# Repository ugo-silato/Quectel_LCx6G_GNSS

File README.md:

# Quectel_LCx6G_GNSS

Arduino library for the **Quectel LC26G, LC26G-T, LC76G and LC86G**
multi-constellation GNSS modules (GPS, GLONASS, Galileo, BeiDou, QZSS),
which share the same Quectel protocol (PAIR / PQTM commands).

Developed and tested on the **LC76G (PA)**: that is why the classes and
the main header are called `LC76G` and `Quectel_LC76G.h`. The other
modules of the family are compatible but not tested, see
[Compatible modules and limitations](#compatible-modules-and-limitations).

> **About the hardware.** The shield in the pictures is the **revision 1
> test prototype** used to develop and test this library: it is **not the
> final design**. An improved revision 2 will follow, fixing the issues
> listed in [Reference shield, revision 1 – known issues](#reference-shield-revision-1--known-issues).
> The library itself does not depend on this board: any LC76G wiring works.
> The KiCad 10 files of the shield (schematic, PCB, BOM) are in
> [hardware](hardware/README.md).

> **Status: 1.0.0.** Every function was tested on the bench with real
> hardware (LC76G (PA) on Arduino Uno R3 and Uno R4 Minima), except the
> few listed under [Test status](#test-status), which need outdoor or
> laboratory tests.

## Features

- UART link through any Arduino `Stream` (`HardwareSerial` or `SoftwareSerial`)
- **I2C link** as an alternative to the UART (`LC76G_I2C`, header-only, used
  like a serial port: every function of the library works the same way)
- Automatic UART baud rate configuration: a brand-new module (115200 baud) is
  switched to the speed you choose, e.g. 38400 for `SoftwareSerial`
- NMEA decoder for **RMC**, **GGA** and **GSV**, integer-only
  (latitude/longitude in degrees × 10⁷, no float precision loss on AVR)
- Satellites in view per constellation and strongest signal (SNR)
- End-of-epoch callback, called once per second
- **PAIR** commands with automatic checksum, acknowledgement (`$PAIR001`)
  handling and query results
- Hot / warm / cold start, baud rate query and change
- NMEA output configuration: choose which sentences are sent and how often,
  or keep only the ones the decoder needs (about 30% less UART traffic with a fix)
- Save the configuration to the module flash
- Constellation selection (GPS, GLONASS, Galileo, BDS, QZSS), limited to
  the combinations supported by the LC76G
- Jamming detection: status messages decoded automatically, optional
  reading of the JAM_IND pin
- PQTM proprietary commands with OK/ERROR handling, PQTM message rates
  (set and read back)
- Output settings: minimum satellite SNR, NMEA decimal places and Talker
  ID, RTCM 3 output configuration (the binary RTCM data itself is not
  decoded), Galileo Return Link Message output, 1PPS / NMEA synchronisation
- PQTM output messages decoded through callbacks, integer-only:
  **PQTMPVT** (position, velocity and time), **PQTMVEL** (velocity with
  accuracy estimates), **PQTMDOP** (all dilution of precision values),
  **PQTMODO** (odometer, with configuration and reset), **PQTMTIMEGPS**
  (GPS week and time of week with accuracy), **PQTMPL** (protection
  levels), **PQTMPOSECEF / PQTMVELECEF / PQTMPVTECEF** (ECEF coordinates).
  A message that is not used costs no RAM and no flash
- Geofence: up to 4 circles or polygons, status messages decoded
  automatically, optional reading of the GEOFENCE pin
- 1PPS (One Pulse Per Second) configuration, and optional pulse measurement
  (count, period, width) on an Arduino interrupt pin
- Low power: navigation mode, ALP (Adaptive Low Power), GLP (GPS Low
  Power), FLP (Fitness Low Power), periodic run/sleep, Backup mode with
  automatic VCC cut and wake-up through the power and reset pins
- AGNSS (Assisted GNSS) without internet: EASY and EPOC orbit prediction,
  navigation data save/clear, reference time and position injection,
  firmware version query
- LOCUS built-in logger (128 KB): modes, thresholds, record count, read-back,
  automatic protection of the recorded data on reboot / power-off
- Reception settings: elevation mask, AIC (Active Interference
  Cancellation), SBAS / DGPS corrections, 2D fix, real-time speed response,
  BDS B1C band, static navigation threshold
- Estimated positioning error (PQTMEPE) in metres, factory reset and
  parameter save (PQTMRESTOREPAR / PQTMSAVEPAR)
- Readable full names for results, NMEA sentences and constellations
- Safe control of the module power and reset pins, with three drive modes
  for different hardware designs
- No dynamic memory, no `String` objects

## Supported boards

| Board | Status |
|---|---|
| Arduino Uno R3 (ATmega328P) | Tested (UART through SoftwareSerial, I2C) |
| Arduino Uno R4 Minima | Tested (UART through Serial1 on D0/D1, I2C); all examples select Serial1 automatically, see "Serial port on the Uno R4" |
| Arduino Uno R4 WiFi | Same core as the Minima, not tested |

On the Uno R3 the `BasicMonitor` example uses about 16.5 KB of flash and
1 KB of RAM (`I2cMonitor`: 18.8 KB and 1.15 KB). Unused features cost
nothing: the PQTM message decoders and the I2C port are linked only when
a sketch uses them.

## Compatible modules and limitations

The library uses the commands of the Quectel *LC26G & LC26G-T & LC76G &
LC86G Series GNSS Protocol Specification* (v1.5), shared by this family:

| Series | Variants covered by the protocol |
|---|---|
| LC26G | LC26G (AB) |
| LC26G-T | LC26G-T (AA) |
| LC76G | LC76G (AB), LC76G (PA), LC76G (PB) |
| LC86G | LC86G (AA), LC86G (AB), LC86G (LA), LC86G (PA) |

**Tested on real hardware: LC76G (PA) only**, firmware
`LC76GPANR12A06S`. The other variants should work for the common
commands, but are not tested.

Known differences between the variants, from the Quectel documentation:

- **Supply and I/O voltage.** LC76G (AB, PA): VCC 2.55–3.6 V, I/O at VCC
  (3.3 V typ.). **LC76G (PB): VCC 1.75–1.98 V, I/O at 1.8 V**, absolute
  maximum 1.98 V on the I/O pins: it needs 1.8 V level shifting and is not
  compatible with the reference shield.
- **Constellations.** LC86G (AA) has no GLONASS and LC86G (AB) has no BDS;
  their accepted search-mode combinations differ from the other variants.
  `setConstellations()` checks the combinations of the LC76G series and may
  refuse valid LC86G (AA/AB) combinations, or accept ones they do not have.
- **Low power modes.** LC26G-T (AA) does not support ALP, FLP and the
  periodic mode (protocol specification). ALP needs a minimum firmware
  version (e.g. LC76G (PA) `LC76GPANR02A02S` or later, Low Power Mode
  Application Note). The Low Power Mode Application Note does not cover
  LC26G-T (AA).
- **Not implemented on purpose.** QZSS SLAS (PAIR420/421, PQTMCFGSLAS,
  PQTMSLAS: sub-metre corrections available only in Japan, partly binary
  output), the binary debug log (PAIR086, needs 921600 baud), PQTMCFGCNST
  (same function as PAIR066, already covered by `setConstellations()`),
  the timing modes PAIR753–765 (LC26G-T only) and the fix rate PAIR050
  (LC76G (PA/PB) are fixed at 1 Hz).
- **PQTM messages and firmware.** Several messages were added in protocol
  v1.5 (PQTMVEL, PQTMTIMEGPS, the ECEF messages, ...): older firmware may
  not have them. On the tested LC76G (PA) `LC76GPANR12A06S` all of them are
  supported except, as the specification says, PQTMANTENNASTATUS and
  PQTMCFGANTENNA (LC26G (AB) / LC86G only), PQTMLS and PQTMUTC (LC26G-T
  only). `getPqtmMessageRate()` answers `LC76G_NOT_SUPPORTED` or
  `LC76G_PARAM_ERROR` for a message the firmware does not know; the
  `TEST_SUPPORT` section of `ShieldTest` checks them all.
- **Orbit prediction.** A firmware has either EASY or EPOC, never both:
  check with `getFirmwareVersion()` and the getters (see AGNSS notes).
- **I2C.** According to the I2C Application Note, I2C is available on
  LC26G (AB), LC26G-T (AA) and the LC76G series only (not on LC86G).

Library limitations, independent of the module:

- LOCUS read-back is incomplete with SoftwareSerial (see LOCUS notes);
  it is complete with a hardware UART.
- With SoftwareSerial the module UART runs at 38400 baud; below that the
  module was observed to drop its own replies.
- Firmware upgrade and network EPO (internet) are out of scope.
- Current consumption values are datasheet figures, not measured.

## Installation

Download this repository as a ZIP and use *Sketch → Include Library →
Add .ZIP Library…* in the Arduino IDE, or clone it into your
`Arduino/libraries` folder. Then `#include <Quectel_LC76G.h>` in your
sketch.

## Quick start

```cpp
#include <SoftwareSerial.h>
#include <Quectel_LC76G.h>

SoftwareSerial gnssSerial(4, 5);   // RX <- module TXD, TX -> module RXD
LC76G gnss;

// Lets the library change the host serial speed (and removes the
// SoftwareSerial RX pull-up, see "Voltage levels")
void openGnssPort(uint32_t baud) {
  gnssSerial.begin(baud);
  LC76G::disableRxPullup(4);
}

void setup() {
  Serial.begin(115200);
  gnss.setPowerPin(6, LC76G_DRIVE_WEAK_PULLUP_HIGH);   // optional
  gnss.begin(gnssSerial, openGnssPort, 38400);         // 115200 -> 38400 if needed
}

void loop() {
  gnss.update();                   // Call as often as possible
  const LC76G_Fix &f = gnss.nmea.fix();
  if (f.valid) {
    // f.latE7, f.lonE7, f.altitudeCm, f.satsUsed, f.hour, ...
  }
}
```

## Examples

| Example | What it shows |
|---|---|
| `BasicMonitor` | Readable summary once per second and status LED |
| `I2cMonitor` | Same as `BasicMonitor`, through I2C instead of the UART |
| `MessageConfig` | Reading and changing the NMEA output, UART traffic measurement |
| `Geofence` | Circle around the first fix, inside/outside from message and pin |
| `JammingDetection` | Jamming status from message and JAM_IND pin |
| `Pps` | 1PPS configuration and pulse measurement on an interrupt pin |
| `LowPower` | ALP, periodic and Backup modes |
| `Agnss` | EASY / EPOC orbit prediction, progress report |
| `Locus` | Start recording, read back as CSV, erase |
| `ReceptionSettings` | Elevation mask, AIC, SBAS / DGPS, 2D fix, other reception settings |
| `ShieldTest` | Bench test of the whole library: enable the tests to run with the `#define TEST_...` lines at the top (on the Uno R3 enable one or two at a time: all together do not fit) |

## NMEA output and the decoder

The decoder needs **RMC** (time, date, position, end-of-epoch marker) and
**GGA** (satellites used, altitude, HDOP). **GSV** is needed only for the
satellites-in-view statistics; if it is sent every N fixes, the last values
are kept in between. Do not disable RMC: without it the epoch callback is
never called.

Settings live in the module RTC RAM and survive power cycles as long as
the backup supply (V_BCKP) stays powered. Without a backup supply, call
`saveSettings()` after changing them.

## Wiring and hardware notes

### Voltage levels

The LC76G I/O runs at **3.3 V**. Uno R3 and Uno R4 are **5 V** boards:

- The module TXD can go straight to an Arduino input. On the Uno R3
  3.3 V is a guaranteed HIGH; on the Uno R4 (RA4M1, HIGH guaranteed only
  above 0.8 × VCC ≈ 4 V) it is outside the guaranteed range and normally
  works, but a level shifter is the safe choice on new designs.
- Arduino TX → module RXD **must** go through a level shifter
  (e.g. a BSS138 stage).
- Never drive a 5 V HIGH directly into a module pin.
- SoftwareSerial (both AVR and Uno R4 versions) enables the internal
  pull-up of its RX pin, which pushes 5 V current into the module TXD
  output and back-powers the module while it is off. Call
  `LC76G::disableRxPullup(rxPin)` right after every `gnssSerial.begin()`,
  as all the examples do.
- Module outputs read by the Arduino (JAM_IND, GEOFENCE, 3D_FIX, 1PPS)
  must be plain `INPUT`, never `INPUT_PULLUP`: the internal pull-up would
  push 5 V into a 3.3 V output. GEOFENCE and 3D_FIX must also not be pulled
  high during the first 50 ms after power-on or reset.

### I2C link

```cpp
#include <Wire.h>
#include <Quectel_LC76G.h>
#include <LC76G_I2C.h>

LC76G_I2C gnssI2c(Wire);
LC76G     gnss;

void setup() {
  gnss.setPowerPin(6, LC76G_DRIVE_WEAK_PULLUP_HIGH);
  gnss.powerOn();                   // FIRST: the shield I2C pull-ups need the module supply
  delay(LC76G_BOOT_MS);
  gnssI2c.begin();                  // 100 kHz, Arduino internal pull-ups OFF
  gnss.begin(gnssI2c, nullptr);     // nullptr: no baud rate on I2C
  gnss.setMinimalNmeaOutput();      // less data to move over I2C
}
void loop() { gnss.update(); }
```

- **Power the module before starting I2C.** On the reference shield the
  I2C pull-ups are supplied by the module rail: with the module off the
  bus sits at 0 V. Starting I2C first, the sketch gave no output at all on
  the Uno R4; powering the module first works.
- Polling: when nothing is waiting the port asks the module every 200 ms
  (`setPollInterval()`); each poll blocks the sketch for about 20 ms.
  After a command it polls every 20 ms for 1.5 s, so replies are not
  delayed. 20 ms and 1000 ms gave the same reception on the bench.
- The module answers at 0x50 (configuration), 0x54 (read) and 0x58
  (write); 0x54 and 0x58 answer only inside a transfer started at 0x50,
  so an I2C scanner shows the module at 0x50 only.
- The module needs **10 ms between two transfers**: without that pause it
  does not acknowledge its address (verified on the bench). `LC76G_I2C`
  waits before every transfer and repeats it up to 20 times, as in the
  Quectel sample code. Reading costs about 20 ms per chunk (32 bytes on
  the Uno R3, limited by the Wire buffer; 128 on the Uno R4), so keep the
  NMEA output small.
- **Voltage.** The module I2C pins work at 3.3 V and the bus must be
  pulled up to 3.3 V (2.2 kΩ on the reference shield). `LC76G_I2C::begin()`
  switches off the Arduino internal pull-ups, which would pull towards 5 V.
  On a 5 V Arduino the 3.3 V high level is below the guaranteed input
  threshold of the I2C pins (0.7 × VCC = 3.5 V on both the ATmega328P and
  the RA4M1): it worked on the bench, but an I2C level shifter is the safe
  choice for a new design.
- The I2C port cannot be used for firmware upgrades (Quectel). The UART
  keeps sending NMEA as well.
- `LC76G_I2C` is header-only, so the Wire library is compiled only into
  the sketches that include `LC76G_I2C.h`.

### Serial port on the Uno R4

On the Uno R4 **SoftwareSerial needs an interrupt-capable RX pin**.
On the R4 Minima these are D0, D1, D2, D3, D8, D12, D13 and A1–A5;
**D4 is not one of them**, so the reference shield (module TXD on D4)
cannot receive through SoftwareSerial on the R4. Use the hardware port
`Serial1` (D0 = RX, D1 = TX) instead, which is also faster and more
reliable. On the rev. 1 shield this needs two wires on the header pins:
D4 → D0 and D5 → D1 (remove them before going back to an Uno R3, where
D0/D1 belong to the USB link). All the examples select `Serial1`
automatically when compiled for the R4.

*Temporary wiring on the rev. 1 shield for the Uno R4: D4 → D0 and D5 → D1.
Revision 2 will replace them with solder jumpers.*

### Power and reset pins

Power and reset control are optional. Configure them **before** `begin()`:

```cpp
gnss.setPowerPin(6, LC76G_DRIVE_WEAK_PULLUP_HIGH);
gnss.setResetPin(3, LC76G_DRIVE_WEAK_PULLUP_HIGH);
```

| Drive mode | Asserted | Released | Use it for |
|---|---|---|---|
| `LC76G_DRIVE_PUSH_PULL_HIGH` | OUTPUT HIGH | OUTPUT LOW | EN input of a load switch or regulator at host voltage |
| `LC76G_DRIVE_WEAK_PULLUP_HIGH` | INPUT_PULLUP | OUTPUT LOW | NPN base wired directly, without a series resistor |
| `LC76G_DRIVE_OPEN_DRAIN_LOW` | OUTPUT LOW | INPUT | Active-low 3.3 V input such as `RESET_N` wired directly |

For the power pin, *asserted* means **module on**. For the reset pin,
*asserted* means **module held in reset**.

Without any control pin, the library still works, but a baud rate change
requires a manual power cycle (`begin()` returns `false` in that case).

### Reference shield, revision 1 – known issues

The library was developed on a custom Uno shield (KiCad design, passive
Molex patch antenna, LC76G module, 3.7 V Li-Po supply with LDO and
switched module rail). **Revision 1 is a test prototype, not a final
product**: an improved revision 2 will follow. Revision 1 has these known
issues, to be fixed in revision 2 (the design files – KiCad 10 project,
schematic PDF, BOM – are in [hardware](hardware/README.md)):

- The power-enable and reset driver transistors have **no series base
  resistor**: use `LC76G_DRIVE_WEAK_PULLUP_HIGH` on both pins.
- The I2C lines have **no level shifter** (pull-ups to 3.3 V only):
  I2C is out of specification with 5 V boards on this revision.
- First batch only: the LDO footprint pinout does not match the XC6206
  regulator (U1 soldered rotated) and the unidirectional TVS diodes D1/D2
  are reversed. Both are already fixed in the published KiCad files
  (XC6206 pinout, bidirectional SMF5.0CA diodes).
- The bases of the power-enable (Q1) and reset (Q4) transistors have **no
  pull-down**: while the Arduino resets or is off, D3 and D6 float. By
  design, when the Arduino is off the module must be off too (Backup
  state: only V_BCKP powered, RTC and satellite data kept); revision 2
  adds base pull-downs to make this state certain.
- The module UART (TXD → Arduino) has no level shifter: fine on the
  Uno R3, outside the guaranteed input level on the Uno R4.
- Using the hardware UART of the Uno R4 needs two wires (D4 → D0,
  D5 → D1): revision 2 adds solder jumpers to choose D4/D5 or D0/D1.
- Do not keep the module powered while the Arduino is off (e.g. with a
  pull-up on PWR_EN_VCC): the module outputs and the I2C pull-ups then
  back-power the Arduino through its pin protection diodes.

## API overview

### `LC76G` (core)

| Method | Description |
|---|---|
| `setPowerPin(pin, mode)` / `setResetPin(pin, mode)` | Optional control pins |
| `begin(port, setHostBaud, targetBaud)` | Power on, boot, baud configuration. Returns `true` when NMEA is received |
| `update()` | Reads and decodes incoming data. Call from `loop()` |
| `powerOn()` / `powerOff()` / `resetPulse()` / `reboot()` | Power and reset |
| `sendRaw(body)` | Sends any sentence, checksum added automatically |
| `sendPair(id, params, timeoutMs, resp, respSize)` | Sends a PAIR command and waits for the result |
| `hotStart()` / `warmStart()` / `coldStart()` | Restart modes |
| `queryBaudRate(baud)` / `setBaudRate(baud)` | UART speed |
| `setNmeaRate(type, rate)` / `getNmeaRate(type, rate)` | Output rate of a sentence: 0 = off, N = every N fixes |
| `setMinimalNmeaOutput(gsvRate)` | Keep only GGA, RMC and GSV |
| `saveSettings()` | Store the configuration in the module flash |
| `setConstellations(mask)` / `getConstellations(mask)` | Systems to search, `LC76G_GNSS_xxx` flags |
| `setJammingDetection(enable)` | Enable/disable jamming detection (send after every power-up) |
| `jammingStatus()` / `jammingStatusMs()` | Last jamming status and when it arrived |
| `setJamIndicatorPin(pin)` / `jamIndicatorActive()` | Optional JAM_IND pin (LOW = jamming) |
| `sendPqtm(name, params, timeoutMs, resp, respSize)` | Sends a PQTM command and waits for OK / ERROR |
| `setPqtmMessageRate(name, rate, msgVer)` / `getPqtmMessageRate(name, msgVer, rate)` | Output rate of a PQTM message; the getter also tells whether the firmware knows it |
| `setGeofenceCircle(index, latE7, lonE7, radiusM)` | Circular geofence (index 0..3) |
| `setGeofencePolygon(index, lat[], lon[], count)` | Triangle or quadrangle geofence |
| `disableGeofence(index)` / `getGeofenceEnabled(index, enabled)` | Disable / read a geofence |
| `setGeofenceStatusOutput(rate)` / `geofenceState(index)` | Status messages and last state (inside / outside / unknown) |
| `setGeofencePin(pin)` / `geofencePinInside()` | Optional GEOFENCE pin (HIGH = inside) |
| `setPps(enable, durationMs, mode, activeHigh)` / `getPps(cfg)` | 1PPS configuration |
| `beginPpsCapture(pin)` | Measure the pulses on an interrupt pin (D2/D3 on Uno R3; D0–D3, D8, D12, D13, A1–A5 on Uno R4 Minima); `false` on other pins |
| `ppsCount()`, `ppsPeriodUs()`, `ppsWidthUs()`, `ppsAgeMs()` | Measured pulse data |
| `setNavigationMode(mode)` / `getNavigationMode(mode)` | Normal, fitness, balloon, stationary, drone, swimming |
| `setAlpMode(0/1/2)` / `getAlpMode(mode)` | Adaptive Low Power (needs normal navigation mode) |
| `setGlpMode(on)` / `setFlpMode(on)` and getters | GPS / Fitness Low Power (need fitness navigation mode) |
| `setPeriodicMode(cfg)` / `getPeriodicMode(cfg)` / `disablePeriodicMode(timeoutMs)` | Run / sleep cycles |
| `enterBackup(seconds)` / `exitBackup()` | Backup mode (about 13 uA on V_BCKP) |
| `getFirmwareVersion(buf, size)` | Firmware version string (PQTMVERNO) |
| `setEasy(on)` / `getEasy(enabled, days)` | EASY orbit prediction (default on), days ready |
| `setEpoc(on)`, `setEpocConstellations(mask)`, `getEpoc(enabled, mask)`, `clearEpocData()`, `getEpocPredictionStatus(bit, status, satsReady)` | EPOC, only on firmwares that support it (e.g. LC76GPANR12A06S) |
| `saveNavigationData()` / `clearNavigationData()` | Navigation data RTC RAM to flash / full clear (cold start) |
| `setReferenceTime(...)` / `setReferencePosition(...)` | Host assistance, to resend after every reboot |
| `setLocusEnabled(on)` / `getLocusEnabled(on)` | Start / stop LOCUS recording |
| `setLocusMode(bits, require3dFix)` / `getLocusMode(...)` | Every fix, time, speed, distance, before sleep, on request |
| `setLocusThreshold(trigger, value)` / `getLocusThreshold(...)` | Threshold of the time / speed / distance modes |
| `clearLocus(what)`, `logLocusNow()`, `getLocusRecordCount(count)` | Erase, record now, number of records |
| `dumpLocus(callback, stats, idleTimeoutMs)` | Read all records, compact format (one line per record), with damaged-record detection |
| `dumpLocusNmea(callback, stats, idleTimeoutMs)` | Read all records as $LOGGA / $LORMC sentences |
| `unixToUtc(t, y, mo, d, h, mi, s)` | Unix time of a LOCUS record to UTC date/time |
| `setElevationMask(deg)` / `getElevationMask(deg)` | Minimum satellite elevation (-90..90, default 5) |
| `setAic(on)` / `getAic(on)` | Active Interference Cancellation |
| `setSbas(on)` / `getSbas(on)` | SBAS satellite search (EGNOS, WAAS, GAGAN, MSAS) |
| `setDgpsSource(src)` / `getDgpsSource(src)` | Correction source: none, SBAS, QZSS SLAS |
| `set2dFix(on)` / `get2dFix(on)` | Allow 2D fixes |
| `setImmediateSpeed(on)` / `getImmediateSpeed(on)` | Real-time speed response |
| `setBdsB1c(on)` / `getBdsB1c(on)` | BDS B1C band tracking |
| `setStaticThreshold(dms)` / `getStaticThreshold(dms)` | Static navigation threshold, dm/s |
| `setEpeOutput(rate)` / `epe()` / `epeAgeMs()` | Estimated positioning error: north, east, down, horizontal, 3D (mm) |
| `set...Output(rate)` / `on...(callback)` for `Pvt`, `Velocity`, `Dop`, `Odometer`, `GpsTime`, `ProtectionLevel`, `EcefPosition`, `EcefVelocity`, `EcefPvt` | PQTM output messages: enable, then receive the decoded structure in a callback (up to `LC76G_OUTPUT_HOOKS` = 6 at the same time) |
| `setOdometer(on, initialDm)` / `getOdometer(on, initialDm)` / `resetOdometer()` | Odometer configuration and reset |
| `setMinSnr(dBHz)` / `getMinSnr(dBHz)` | Minimum SNR of the satellites used (9..37, default 9) |
| `setNmeaDecimals(d)` / `getNmeaDecimals(d)` | Decimal places of the NMEA fields |
| `setNmeaTalkerId(id, gsvSameAsMain)` / `getNmeaTalkerId(id, gsvSameAsMain)` | Talker ID ("00" = automatic) |
| `setRtcmMode(mode)`, `setRtcmAntennaPoint(on)`, `setRtcmEphemeris(on)` and getters | RTCM 3 output (binary, not decoded) |
| `setRlmOutput(on)` / `getRlmOutput(on)` | Galileo Return Link Message ($GARLM) |
| `setPpsNmeaSync(on)` | 1PPS / NMEA delay fixed at 350 ms |
| `restoreDefaults()` | Factory reset of all parameters except baud rate and LOCUS, then reboot (`LC76G_NO_REBOOT` without a power/reset pin: power-cycle manually) |
| `saveParameters()` | Save the configuration to flash (PQTMSAVEPAR) |
| `resultText()`, `nmeaTypeName()`, `constellationName()`, `jamStatusText()`, `geofenceStateText()`, `ppsModeText()`, `navModeText()`, `periodicModeText()`, `dgpsSourceText()`, `rtcmModeText()`, `fixQualityText()` | Full names, stored in flash |
| `isTalking(silenceMs)` | `true` if valid data arrived recently |
| `LC76G::disableRxPullup(rxPin)` | Removes the SoftwareSerial RX pull-up (AVR and Renesas) |
| `onSentence(callback)` | Called for every valid sentence. Callbacks run inside `update()`: they must not send commands (set a flag, send from `loop()`) |
| `LC76G::checksumOk(body)` | Checks the XOR checksum of a sentence |

### `LC76G_I2C` (I2C port, `#include <LC76G_I2C.h>`)

| Method | Description |
|---|---|
| `LC76G_I2C(wire)` | Port on a `TwoWire` bus (default `Wire`) |
| `begin(clockHz, keepInternalPullups)` | Starts I2C (default 100 kHz, internal pull-ups off) |
| `setPollInterval(ms)` | How often the module is asked for data when nothing is waiting (default 200 ms) |
| `errors()` | Transfers that failed after all the attempts |
| Stream methods | `available()`, `read()`, `peek()`, `write()`, `flush()`: used by `LC76G` |

### `LC76G_Result`

`LC76G_OK`, `LC76G_PROCESSING`, `LC76G_FAILED`, `LC76G_NOT_SUPPORTED`,
`LC76G_PARAM_ERROR`, `LC76G_BUSY` (values 0–5 from `$PAIR001`), plus the
local codes `LC76G_TIMEOUT`, `LC76G_NO_PORT`, `LC76G_NO_REBOOT`.

### `gnss.nmea` (decoder)

| Method | Description |
|---|---|
| `fix()` | `LC76G_Fix` structure: status, position, altitude, HDOP, speed, course, UTC date/time |
| `satsInView(system)` / `satsInViewTotal()` | Satellites in view in the last epoch |
| `maxSnr()` | Strongest signal in the last epoch, dB-Hz |
| `onEpoch(callback)` | Called once per epoch, after RMC |
| `latitudeDeg()`, `longitudeDeg()`, `altitudeM()`, `speedKmh()` | Float conversions for printing |

## Start-up and command retries

After power-on or reset, the module sends NMEA sentences before it is
ready to accept commands. `begin()` therefore also waits (up to 5 s,
`LC76G_READY_MS`) until the module answers a harmless PAIR query (PQTM commands are
answered a few seconds earlier than PAIR commands); the wait ends as
soon as the module answers. In addition, every command
that gets no answer is sent again once (`setCommandRetries()` changes
the number of retries).

## Power consumption

The current values in the source code and in this document are the
**typical values of the LC76G (PA) datasheet** for the module alone.
The real consumption of a board also depends on its design (regulator
quiescent current, pull-up resistors, level shifters, protection diodes,
antenna circuit) and **must be measured in a laboratory** on the actual
hardware. Measurements on the reference shield have not been made yet.

Note: the FLP (Fitness Low Power) status can be read only when the
navigation mode is *fitness*; in other modes the module answers "failed".

## 1PPS notes

1PPS on the reference shield, measured on the oscilloscope: 1.0000 Hz,
100 ms pulse (10 % duty, the default `setPps()` duration), 3.34 V high
level, 807 ns rise time. `beginPpsCapture()` measured the same period and
width on the Arduino (about -125 ppm on the Uno R4 Minima, whose clock is
the internal RC oscillator, not a crystal).

## Odometer notes

The odometer adds up every change of position, also the noise of a
stationary receiver: indoors, with a weak signal, it was seen to count
about 15 m in a few seconds with the board standing still. For a fixed
or slow device set a static threshold first, e.g.
`setStaticThreshold(5)` (0.5 m/s): below that speed the module keeps the
position still and the odometer stops counting the noise. The travelled
distance restarts from 0 when the module is switched off or with
`resetOdometer()`.

## LOCUS notes

LOCUS must be stopped before the module is powered off or restarted,
otherwise the recorded data is lost (Quectel protocol specification).
The library stops it automatically in `reboot()`, `powerOff()`,
`enterBackup()` and `setConstellations()`. It cannot protect the data
from an **uncontrolled** loss of the module supply: on the reference
shield the module is switched off whenever the Arduino resets or loses
power (on the Uno R3 also when the Serial Monitor is opened), so a
recording in progress is lost in that case. To read a recording back
without resetting the Arduino, `ShieldTest` (TEST_LOCUS) stops and reads
it when you type `d` in the Serial Monitor.

**Limitation – read-back with SoftwareSerial.** During a read-back the
module streams the records without pauses. With SoftwareSerial (e.g. on
the Uno R3) the host has almost no processing time left and part of the
records is lost: in the tests about 75% of the sentences arrived with the
NMEA format, much less with the compact format, which needs more
processing per record. Lowering the module UART speed for the read-back
was tried and does not work: at 9600 and 19200 baud the module drops its
own replies. The library silences the live NMEA output during the
read-back, checks every record and reports in `stats` whether the
read-back is complete. **A reliable read-back requires a hardware UART**
(e.g. Serial1 on the Uno R4). Recording itself works on any board.

Compact record fields: altitude in metres, HDOP x 100 and heading in
degrees x 100 were verified against the NMEA read-back of the same
records; the speed scale is not verified yet.

## AGNSS notes

EASY (Embedded Assist System) is enabled by default: after a fix, the
module predicts the satellite orbits for up to 3 days, which shortens
later starts. EASY and EPOC (Enhanced Prediction Orbit on Chip) never
coexist in the same firmware. As stated in the Quectel AGNSS Application
Note, assistance cannot compensate for a signal that is too weak:
indoors, a slow first fix is usually a signal problem.

## Test status

Hardware: LC76G (PA), firmware `LC76GPANR12A06S`, on the reference shield
rev. 1 with an Arduino Uno R3 and an Arduino Uno R4 Minima.

**Tested on the bench:** start-up and automatic baud configuration
(including the wait until the module accepts commands, with the module
restarting at every Arduino reset), NMEA
decoder (RMC, GGA, GSV), NMEA output configuration, constellation
selection, jamming detection (status message and JAM_IND pin, "no
jamming" condition only), 1PPS configuration and pulse measurement, ALP
mode 1, AGNSS detection (EASY / EPOC) and EPOC configuration, LOCUS
recording, reception settings (set and read back), factory reset,
estimated positioning error (without fix), I2C link (`I2cMonitor`).

**Tested on the Uno R4 Minima** (module on Serial1, D0/D1, see
"Serial port on the Uno R4"): start-up and baud configuration, NMEA
output configuration, constellation selection (with module reboot),
jamming detection (message and JAM_IND pin on D8), 1PPS capture on D2,
reception settings, factory reset, AGNSS / EPOC detection and configuration, estimated positioning error, PQTMPVT / PQTMVEL / PQTMDOP / PQTMODO / PQTMTIMEGPS / PQTMPL / ECEF messages, output settings (minimum SNR, NMEA decimals and Talker ID, RTCM, RLM),
I2C link (`TEST_I2C`, `I2cMonitor`, fix with the same SNR as the UART),
the `BasicMonitor` example, and a
**complete LOCUS read-back** (87 records announced, 87 received,
0 damaged).

**Not tested yet:**

- Periodic power saving mode and Backup mode (enter / wake-up)
- GLP and FLP modes
- Geofence inside → outside transition
- SBAS / EGNOS corrections (fix quality "DGPS")
- Estimated positioning error with a valid fix
- Time to first fix after a night with EPOC
- Speed field of the compact LOCUS records (scale not verified)
- On the Uno R4: geofence, low power modes, AGNSS prediction progress (bench tests not repeated)
- Uno R4 WiFi
- Current consumption measurements

## Roadmap

- [x] Core: UART, checksum, PAIR commands, baud rate configuration
- [x] NMEA decoder: RMC, GGA, GSV
- [x] Standard NMEA output rates (PAIR062 / PAIR063)
- [x] PQTM commands and message rates (`PQTMCFGMSGRATE`)
- [x] Constellation selection (PAIR066 / PAIR067)
- [x] Geofence (PQTMCFGGEOFENCE, $PQTMGEOFENCESTATUS, GEOFENCE pin) – **not field-tested**:
  creation and the "inside" state verified indoors (message and pin agree);
  the inside → outside transition has not been tested
- [x] Jamming detection (PAIR391, $PAIRSPF, JAM_IND pin)
- [x] Low power modes (ALP, GLP, FLP, periodic, Backup)
- [x] 1PPS configuration (PQTMCFGPPS) and pulse capture
- [x] LOCUS data logging (PAIR900–PAIR909)
- [x] AGNSS: EASY, EPOC, navigation data, reference time and position
  (network EPO files out of scope)
- [x] Reception settings (PAIR070–075, PAIR158–163, PAIR400/401, PAIR410/411) – field test pending
- [x] Estimated positioning error, factory reset, parameter save
- [x] Uno R4 Minima testing
- [x] PQTMPVT, PQTMVEL, PQTMDOP output messages
- [x] Odometer (PQTMCFGODO / PQTMRESETODO / PQTMODO), GPS time (PQTMTIMEGPS),
  protection level (PQTMPL), ECEF messages (PQTMPOSECEF / VELECEF / PVTECEF)
- [x] Minimum SNR (PAIR058/059), NMEA decimal places and Talker ID
  (PQTMCFGNMEADP / PQTMCFGNMEATID), RTCM output configuration (PAIR432–437),
  Galileo RLM output (PAIR154/155), 1PPS/NMEA sync (PAIR751)
- [x] I2C transport (`LC76G_I2C`) – tested with `I2cMonitor` on the Uno R4 Minima (fix, SNR as on the UART) and on the Uno R3 (32-byte reads keep up with the minimal NMEA output)

Firmware upgrade and EPO download are out of scope: they need more memory
or an internet connection than the target boards provide.

## License

MIT – see [LICENSE](LICENSE). The license covers both the library and the
hardware files in `hardware`.

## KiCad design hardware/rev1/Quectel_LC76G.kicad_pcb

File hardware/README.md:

# Reference shield – hardware files

KiCad 10 design of the Arduino Uno shield used to develop and test the
**Quectel_LCx6G_GNSS** library.

> **Revision 1 is a test prototype, not a final design.** It works (every
> library function was tested on it), but it has the known issues listed
> below. An improved **revision 2** will follow; its files will be added in
> a separate `rev2/` folder.

## Folder content

| Path | Content |
|---|---|
| `rev1/Quectel_LC76G.kicad_pro` | KiCad 10 project |
| `rev1/Quectel_LC76G.kicad_sch` | Root schematic sheet |
| `rev1/01_Power_Supply.kicad_sch` | LDO, switched module rail (VCC_GNSS), backup rail (V_BCKP) |
| `rev1/02_MCU_Interface.kicad_sch` | Uno shield connector, UART level shifter (RXD) |
| `rev1/03_GNSS_Module.kicad_sch` | LC76G module, RESET_N driver, I2C pull-ups, test points |
| `rev1/04_Passive_Antenna.kicad_sch` | Molex patch antenna, matching network, optional SAW filter (DNP) |
| `rev1/Quectel_LC76G.kicad_pcb` | PCB layout |
| `rev1/Quectel_LC76G_schematic.pdf` | Schematic, all sheets (readable without KiCad) |
| `rev1/Quectel_LC76G.csv` | Bill of materials, with LCSC part numbers |

The custom symbols and footprints (LC76G module, Molex antenna, SAW filter)
are embedded in the schematic and PCB files: the project opens in KiCad 10
without any extra library.

## Board summary

| Item | Value |
|---|---|
| Layers | 2, FR4 1.6 mm, 1 oz copper, GND pour on both sides |
| GNSS module | Quectel LC76G (PA), UART + I2C (SPI not used) |
| Antenna | Molex 211624-0001 passive patch, RHCP, 50 Ω, π matching network |
| RF line | Coplanar, 0.92 mm width, no vias; ESD diode RCLAMP0521P |
| Supply | 3.7 V Li-ion/Li-Po cell on BT1 → XC6206 3.3 V LDO |
| Module rail | VCC_GNSS switched by a P-MOSFET with soft start, driven by PWR_EN_VCC (D3) |
| Backup rail | V_BCKP always powered (RTC and satellite data kept with the module off) |
| Reset | RESET_N driven by an open-collector NPN (D6) |
| UART | Module TXD → D4, D5 → module RXD through a BSS138 level shifter |
| I2C | 2.2 kΩ pull-ups to the module rail |
| Test points | RESET_N, TXD, RXD, 1PPS, V_BCKP, VCC_GNSS, I2C_SDA, I2C_SCL, GND |

## Revision 1 – files vs. first batch of boards

The files in `rev1/` include two fixes compared to the first batch of
boards (the one in the pictures):

| Part | Files in `rev1/` | First-batch boards |
|---|---|---|
| U1 (XC6206P332MR, LCSC C5148692) | Footprint with the XC6206 pinout (1 GND, 2 VOUT, 3 VIN) | Footprint with the AP2204R pinout: U1 soldered rotated by hand |
| D1/D2 (TVS on VCC_3.3 and VCC_GNSS) | SMF5.0CA bidirectional (LCSC C908214), no polarity | SMF5.0A unidirectional (C908213), cathode pad on GND: diodes rotated by 180° |

Known issues still present in `rev1/`, to be fixed in revision 2 (see also
[Reference shield, revision 1 – known issues](../README.md#reference-shield-revision-1--known-issues)):

- **Q1/Q4**: no series base resistor and no base pull-down. Use
  `LC76G_DRIVE_WEAK_PULLUP_HIGH` on both control pins.
- **No level shifter** on I2C and on the module TXD line (3.3 V signals
  to a 5 V Arduino).
- **Uno R4**: the hardware UART needs two wires (D4 → D0, D5 → D1).

## Planned for revision 2

- Series base resistors and base pull-downs on Q1/Q4
- Level shifters on I2C and on the module TXD line
- Solder jumpers to choose D4/D5 or D0/D1 for the UART
- LED showing the fix status

## License

These hardware files are released under the same MIT license as the
library, see [LICENSE](../LICENSE). They are provided as they are,
without any warranty: check the design before building it.

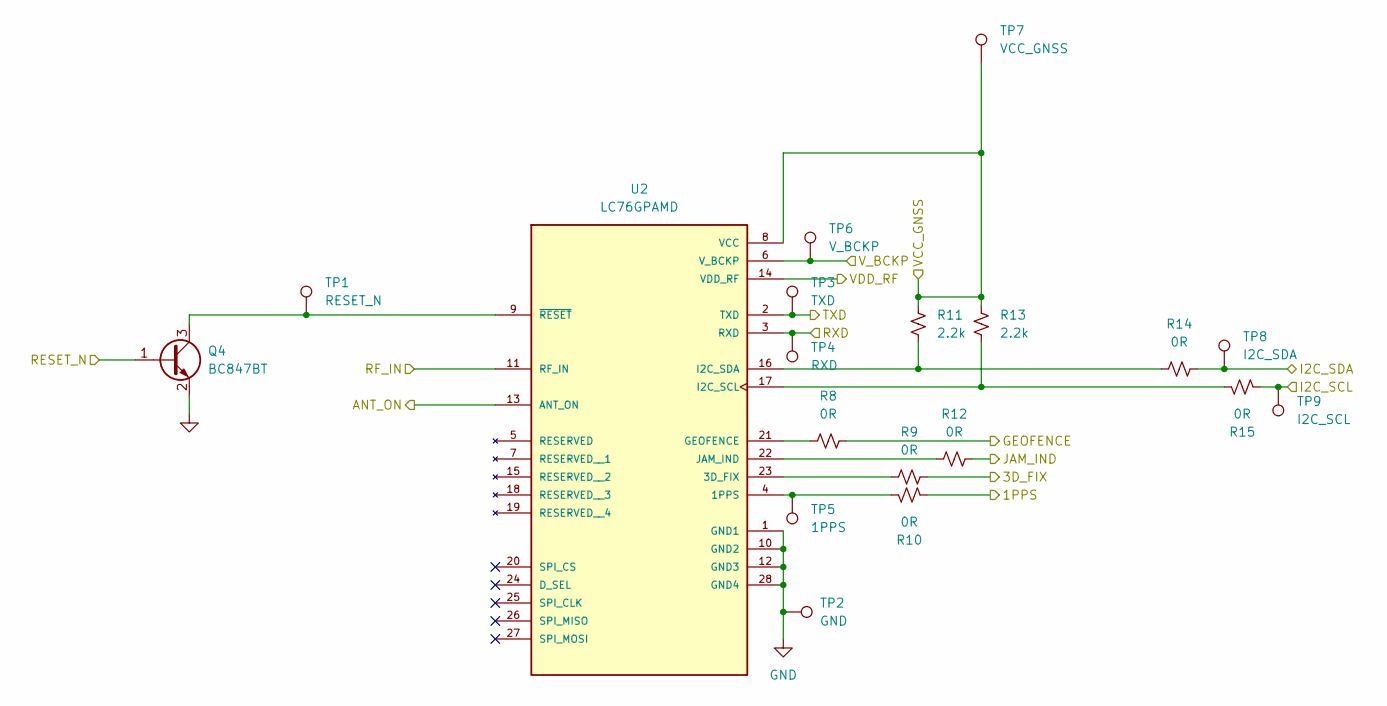
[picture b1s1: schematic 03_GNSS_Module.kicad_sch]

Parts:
Q4: BC847BT; SOT-523; LCSC C21714156
R8, R9, R10, R12, R14, R15: 0R; R_0805_2012Metric_Pad1.20x1.40mm_HandSolder; LCSC C25275
R11, R13: 2.2k; R_0805_2012Metric_Pad1.20x1.40mm_HandSolder; LCSC C17520
TP1: RESET_N; TestPoint_Loop_D2.60mm_Drill1.6mm_Beaded; LCSC C5199805
TP2: GND; TestPoint_Loop_D2.60mm_Drill1.6mm_Beaded; LCSC C5199805
TP3: TXD; TestPoint_Loop_D2.60mm_Drill1.6mm_Beaded; LCSC C5199805
TP4: RXD; TestPoint_Loop_D2.60mm_Drill1.6mm_Beaded; LCSC C5199805
TP5: 1PPS; TestPoint_Loop_D2.60mm_Drill1.6mm_Beaded; LCSC C5199805
TP6: V_BCKP; TestPoint_Loop_D2.60mm_Drill1.6mm_Beaded; LCSC C5199805
TP7: VCC_GNSS; TestPoint_Loop_D2.60mm_Drill1.6mm_Beaded; LCSC C5199805
TP8: I2C_SDA; TestPoint_Loop_D2.60mm_Drill1.6mm_Beaded; LCSC C5199805
TP9: I2C_SCL; TestPoint_Loop_D2.60mm_Drill1.6mm_Beaded; LCSC C5199805
U2: LC76GPAMD; Quectel_LC76G; PARTREV 1.2; LCSC C20607017

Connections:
/01_Power_Supply/VCC_3.3: TP6.1 (1_1), U2.6 (V_BCKP); also elsewhere on the board
/01_Power_Supply/VCC_GNSS: R11.2, R13.2, TP7.1 (1_1), U2.8 (VCC); also elsewhere on the board
/02_MCU_Interface/1PPS: R10.2; also elsewhere on the board
/02_MCU_Interface/3D_FIX: R9.1; also elsewhere on the board
/02_MCU_Interface/GEOFENCE: R8.1; also elsewhere on the board
/02_MCU_Interface/I2C_SCL: R15.2, TP9.1 (1_1); also elsewhere on the board
/02_MCU_Interface/I2C_SDA: R14.1, TP8.1 (1_1); also elsewhere on the board
/02_MCU_Interface/JAM_IND: R12.1; also elsewhere on the board
/02_MCU_Interface/RESET_N: Q4.1 (B); also elsewhere on the board
/02_MCU_Interface/RXD: TP4.1 (1_1), U2.3 (RXD); also elsewhere on the board
/02_MCU_Interface/TXD: TP3.1 (1_1), U2.2 (TXD); also elsewhere on the board
/03_GNSS_Module/ANT_ON: U2.13 (ANT_ON)
/03_GNSS_Module/RF_IN: U2.11 (RF_IN); also elsewhere on the board
/03_GNSS_Module/VDD_RF: U2.14 (VDD_RF)
GND: Q4.2 (E), TP2.1 (1_1), U2.1 (GND1), U2.10 (GND2), U2.12 (GND3), U2.28 (GND4); also elsewhere on the board
unnamed: Q4.3 (C), TP1.1 (1_1), U2.9 (~RESET)
unnamed: R10.1, TP5.1 (1_1), U2.4 (1PPS)
unnamed: R9.2, U2.23 (3D_FIX)
unnamed: R8.2, U2.21 (GEOFENCE)
unnamed: R13.1, R15.1, U2.17 (I2C_SCL)
unnamed: R11.1, R14.2, U2.16 (I2C_SDA)
unnamed: R12.2, U2.22 (JAM_IND)

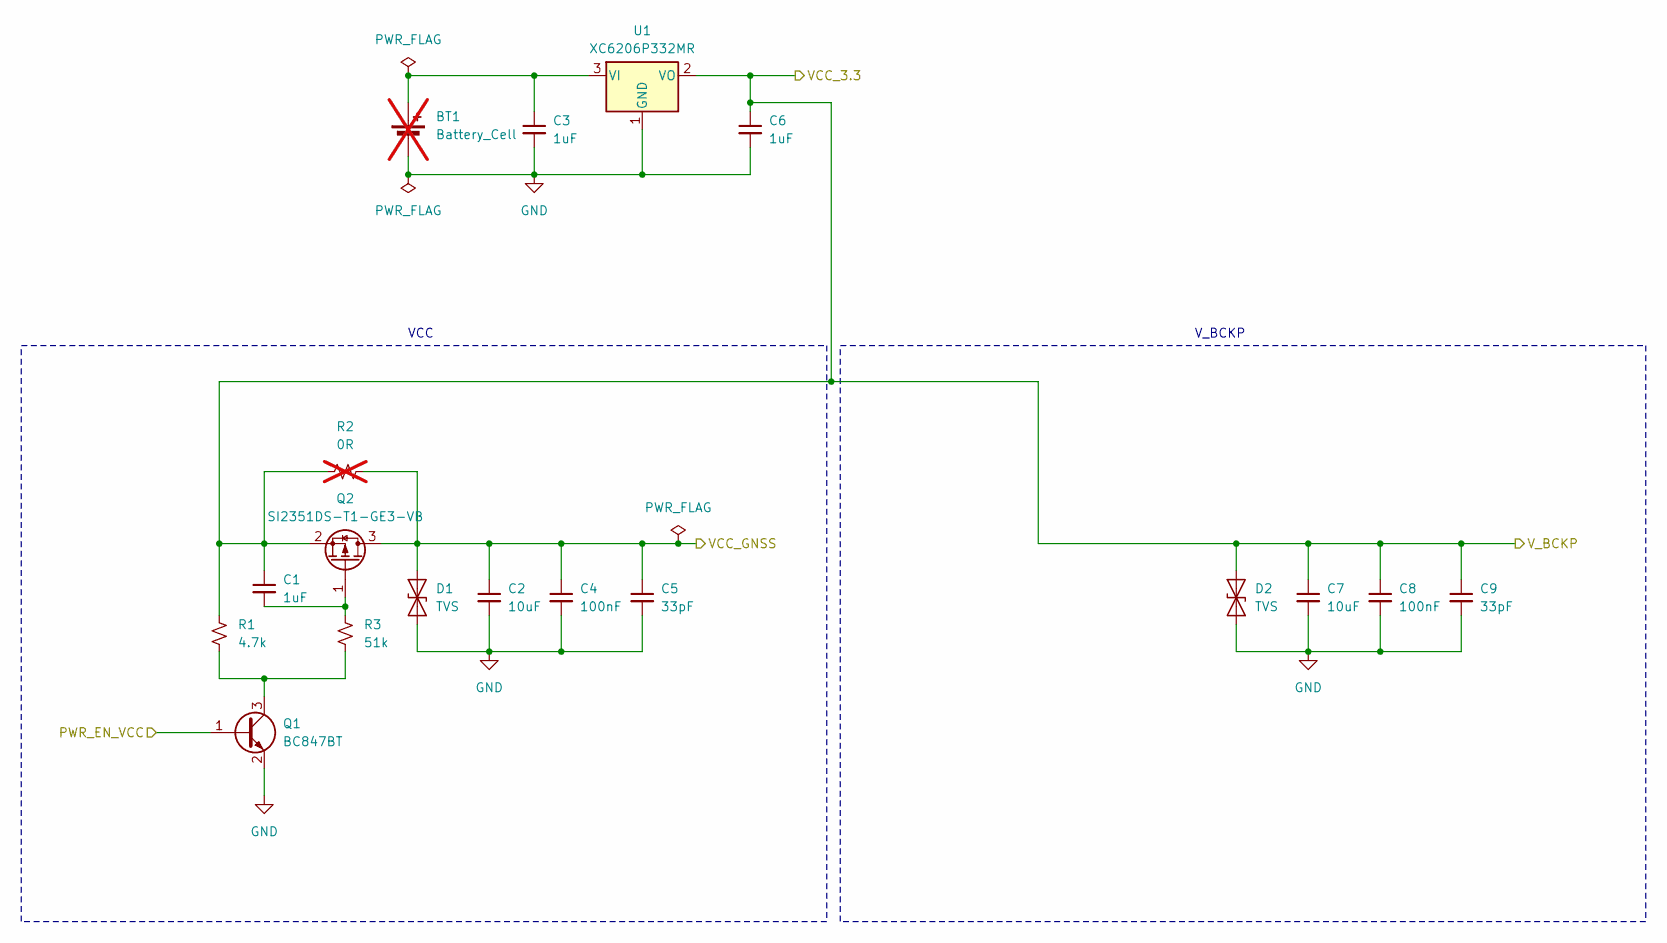
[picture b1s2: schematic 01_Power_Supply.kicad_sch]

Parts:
BT1: Battery_Cell; JST_EH_B2B-EH-A_1x02_P2.50mm_Vertical; LCSC C158012; not fitted
C1, C3, C6: 1uF; C_0805_2012Metric_Pad1.18x1.45mm_HandSolder; LCSC C24123
C2, C7: 10uF; C_0805_2012Metric_Pad1.18x1.45mm_HandSolder; LCSC C1713
C4, C8: 100nF; C_0805_2012Metric_Pad1.18x1.45mm_HandSolder; LCSC C1711
C5, C9: 33pF; C_0805_2012Metric_Pad1.18x1.45mm_HandSolder; LCSC C5186746
D1, D2: TVS; D_SOD-123; LCSC C908214
Q1: BC847BT; SOT-523; LCSC C21714156
Q2: SI2351DS-T1-GE3-VB; SOT-23-3; LCSC C5456591
R1: 4.7k; R_0805_2012Metric_Pad1.20x1.40mm_HandSolder; LCSC C17673
R2: 0R; R_0805_2012Metric_Pad1.20x1.40mm_HandSolder; not fitted
R3: 51k; R_0805_2012Metric_Pad1.20x1.40mm_HandSolder; LCSC C365321
U1: XC6206P332MR; SOT-23-3; LCSC C5148692

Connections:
/01_Power_Supply/PWR_EN_VCC: Q1.1 (B); also elsewhere on the board
/01_Power_Supply/VCC_3.3: C1.1, C6.1, C7.1, C8.1, C9.1, D2.2 (A2), Q2.2 (S), R1.1, R2.1, U1.2 (VO); also elsewhere on the board
/01_Power_Supply/VCC_GNSS: C2.1, C4.1, C5.1, D1.2 (A2), Q2.3 (D), R2.2; also elsewhere on the board
GND: BT1.2 (-), C2.2, C3.2, C4.2, C5.2, C6.2, C7.2, C8.2, C9.2, D1.1 (A1), D2.1 (A1), Q1.2 (E), U1.1 (GND); also elsewhere on the board
unnamed: BT1.1 (+), C3.1, U1.3 (VI)
unnamed: Q1.3 (C), R1.2, R3.2
unnamed: C1.2, Q2.1 (G), R3.1

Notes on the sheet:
V_BCKP
VCC

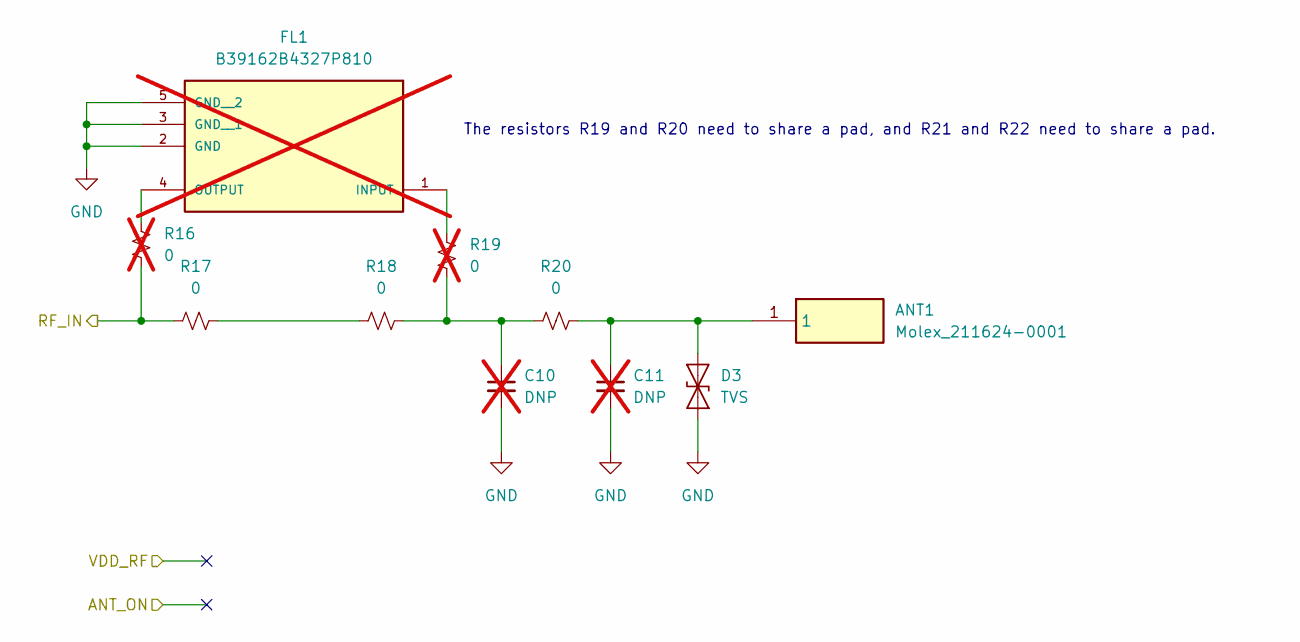
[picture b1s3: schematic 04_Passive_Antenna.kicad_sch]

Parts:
ANT1: Molex_211624-0001; Molex_2116240001; Mouser Part Number 538-211624-0001
C10, C11: DNP; C_0402_1005Metric_Pad0.74x0.62mm_HandSolder; not fitted
D3: TVS; D_0402_1005Metric_Pad0.77x0.64mm_HandSolder; LCSC C3029033
FL1: B39162B4327P810; PARTREV October 25, 2019; DigiKey_Part_Number 495-7424-1-ND; not fitted
R16, R19: 0; R_0402_1005Metric_Pad0.72x0.64mm_HandSolder; not fitted
R17, R18, R20: 0; R_0402_1005Metric_Pad0.72x0.64mm_HandSolder; LCSC C242160

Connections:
/03_GNSS_Module/RF_IN: R16.2, R17.2; also elsewhere on the board
GND: C10.2, C11.2, D3.1 (A1), FL1.2 (GND), FL1.3 (GND__1), FL1.5 (GND__2); also elsewhere on the board
unnamed: C10.1, R18.1, R19.2, R20.2
unnamed: ANT1.1 (1_1), C11.1, D3.2 (A2), R20.1
unnamed: FL1.1 (INPUT), R19.1
unnamed: FL1.4 (OUTPUT), R16.1
unnamed: R17.1, R18.2

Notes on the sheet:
The resistors R19 and R20 need to share a pad, and R21 and R22 need to share a pad.

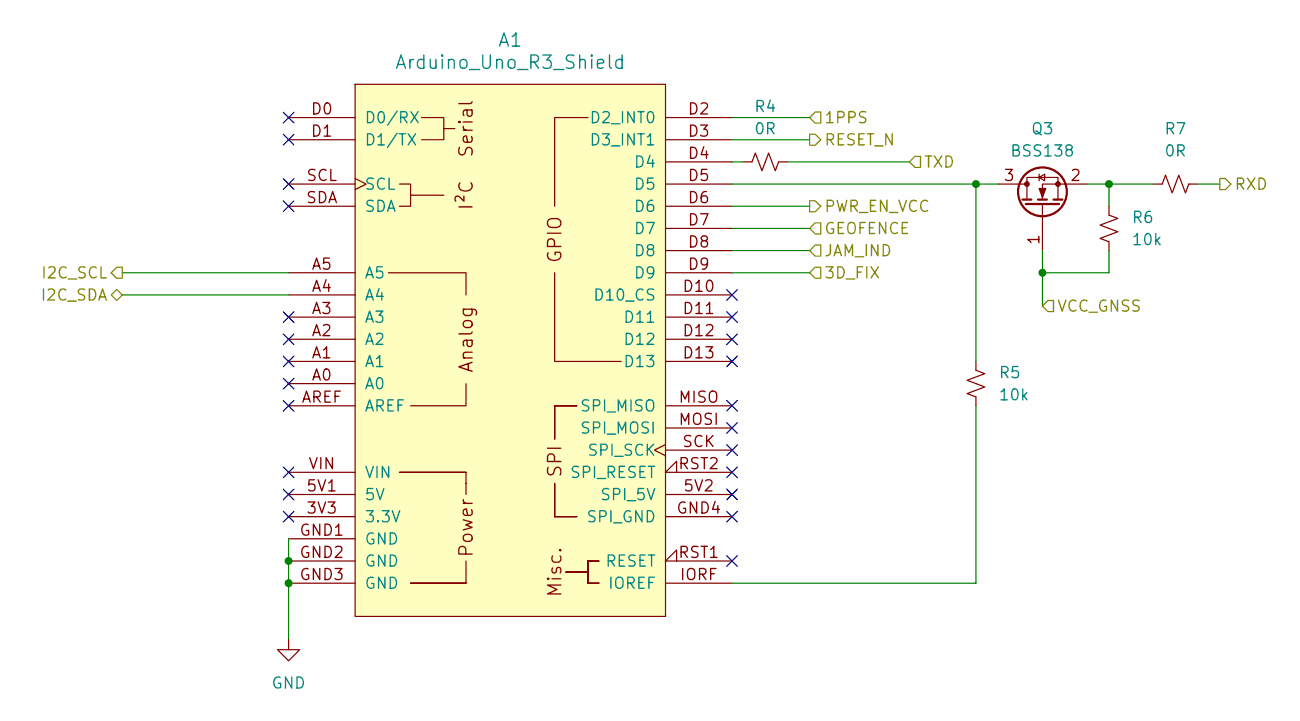
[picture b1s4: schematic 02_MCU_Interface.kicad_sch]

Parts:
A1: Arduino_Uno_R3_Shield
Q3: BSS138; SOT-23; LCSC C431507
R4, R7: 0R; R_0805_2012Metric_Pad1.20x1.40mm_HandSolder; LCSC C25275
R5, R6: 10k; R_0805_2012Metric_Pad1.20x1.40mm_HandSolder; LCSC C17414

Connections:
/01_Power_Supply/PWR_EN_VCC: A1.D6; also elsewhere on the board
/01_Power_Supply/VCC_GNSS: Q3.1 (G), R6.1; also elsewhere on the board
/02_MCU_Interface/1PPS: A1.D2 (D2_INT0); also elsewhere on the board
/02_MCU_Interface/3D_FIX: A1.D9; also elsewhere on the board
/02_MCU_Interface/GEOFENCE: A1.D7; also elsewhere on the board
/02_MCU_Interface/I2C_SCL: A1.A5; also elsewhere on the board
/02_MCU_Interface/I2C_SDA: A1.A4; also elsewhere on the board
/02_MCU_Interface/JAM_IND: A1.D8; also elsewhere on the board
/02_MCU_Interface/RESET_N: A1.D3 (D3_INT1); also elsewhere on the board
/02_MCU_Interface/RXD: R7.1; also elsewhere on the board
/02_MCU_Interface/TXD: R4.1; also elsewhere on the board
GND: A1.GND1 (GND), A1.GND2 (GND), A1.GND3 (GND); also elsewhere on the board
unnamed: A1.IORF (IOREF), R5.1
unnamed: A1.D4, R4.2
unnamed: A1.D5, Q3.3 (D), R5.2
unnamed: Q3.2 (S), R6.2, R7.2

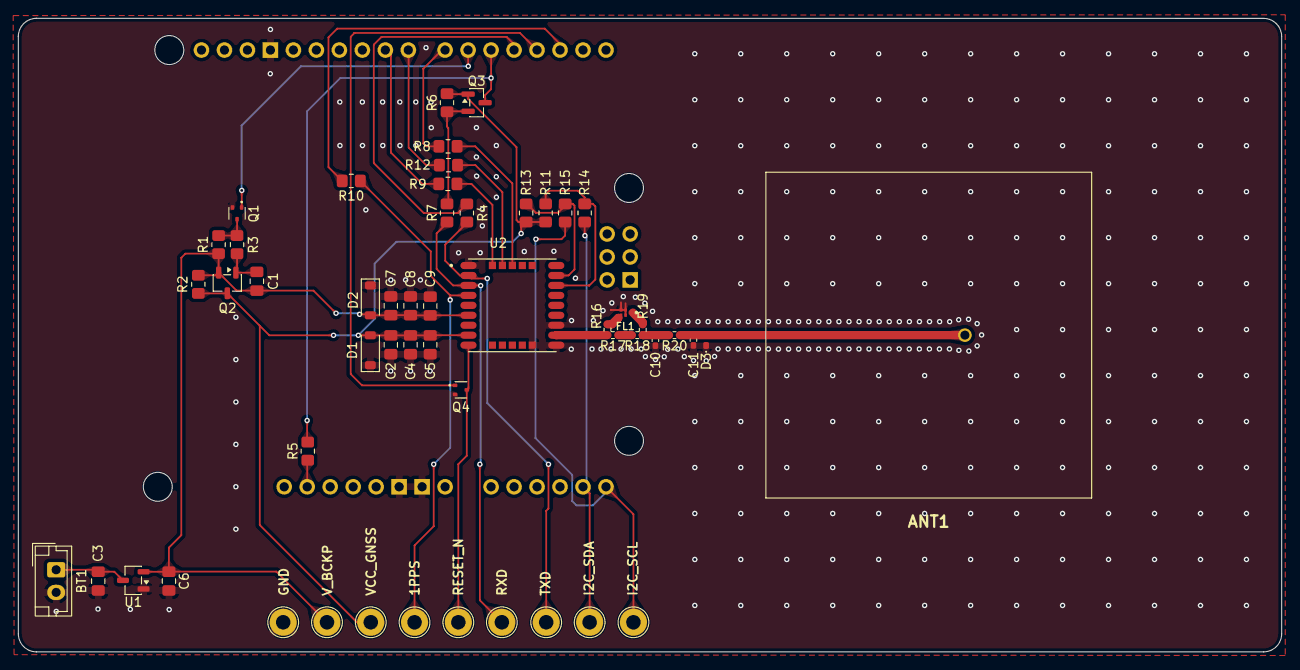
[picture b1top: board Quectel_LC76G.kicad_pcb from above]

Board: 2 copper layers, 139.6 x 70.0 mm, 53 parts (0 on the bottom side), 33 nets.

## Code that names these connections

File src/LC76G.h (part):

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#define LC76G_GEOFENCE_COUNT 4     // Geofences 0..3

enum LC76G_GeofenceState : uint8_t {
  LC76G_GEO_UNKNOWN = 0,           // Geofence disabled, or no position fix
  LC76G_GEO_INSIDE  = 1,           // Receiver inside the area
  LC76G_GEO_OUTSIDE = 2            // Receiver outside the area
};
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  // millis() timestamp of the last status message (0 = none yet)
  unsigned long jammingStatusMs() const { return _jamStatusMs; }

  // Optional: Arduino pin wired to the module JAM_IND output.
  // The pin is configured as a plain INPUT: NEVER enable the internal
  // pull-up, it would push 5 V into a 3.3 V module output.
  void setJamIndicatorPin(int8_t pin);
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  // millis() timestamp of the last status message (0 = none yet)
  unsigned long geofenceStatusMs() const { return _geoStatusMs; }

  // Optional: Arduino pin wired to the module GEOFENCE output
  // (HIGH = inside the active area(s)). Configured as a plain INPUT:
  // the module must not see a pull-up in the first 50 ms after power-on.
  void setGeofencePin(int8_t pin);

  // true if the GEOFENCE pin is HIGH (false if no pin is configured)
  bool geofencePinInside() const;

  // e.g. LC76G_GEO_OUTSIDE -> "outside"
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  // The module cannot receive commands while in Backup mode.
  LC76G_Result enterBackup(uint32_t seconds = 0);

  // Leaves Backup mode: restores VCC (power pin), pulses RESET_N for
  // 100 ms (reset pin) and waits for the first NMEA sentence.
  LC76G_Result exitBackup();

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

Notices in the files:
src/LC76G.h:
License: MIT (see LICENSE file)
